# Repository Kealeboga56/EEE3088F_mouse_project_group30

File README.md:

# Micromouse Project: Sensing and Power Subsystems

This repository contains the design files, schematics, and other relevant resources for the sensing and power subsystems of the Micromouse project. The repository is organized into two main folders: `sensing` and `power`.

## Sensing Subsystem

The `sensing` folder contains all the files related to the design and implementation of the sensing subsystem, responsible for obstacle detection and navigation. It includes the following:

- `schematics/`: This directory contains the schematic files for the sensing circuit, including the main schematic and any supplementary schematics.
- `pcb/`: This directory houses the PCB design files, including the board layout, Gerber files, and any other relevant PCB design files.
- `firmware/`: This directory contains the firmware code for the microcontroller used in the sensing subsystem, along with any libraries or dependencies required.
- `simulations/`: This directory includes any simulation files or models used for testing and validating the sensing subsystem's performance.
- `datasheets/`: This directory contains datasheets for the components used in the sensing subsystem, such as sensors, microcontrollers, and other integrated circuits.
- `docs/`: This directory houses any additional documentation or reports related to the sensing subsystem, such as design specifications, test reports, or user manuals.

## Power Subsystem

The `power` folder contains all the files related to the design and implementation of the power subsystem, responsible for power management and distribution. It includes the following:

- `schematics/`: This directory contains the schematic files for the power circuit, including the main schematic and any supplementary schematics.
- `pcb/`: This directory houses the PCB design files for the power subsystem, including the board layout, Gerber files, and any other relevant PCB design files.
- `firmware/`: This directory contains the firmware code for the microcontroller used in the power subsystem (if applicable), along with any libraries or dependencies required.
- `simulations/`: This directory includes any simulation files or models used for testing and validating the power subsystem's performance.
- `datasheets/`: This directory contains datasheets for the components used in the power subsystem, such as regulators, batteries, and other power management components.
- `docs/`: This directory houses any additional documentation or reports related to the power subsystem, such as design specifications, test reports, or user manuals.

## Importing footprints
- For importing footprints in kicad. the easyeda2kicad script was used.
- `Installation/`: run : "pip install easyeda2kicad" on your terminal
- for more on how to get the lcsc_id and how to import visit website [https://pypi.org/project/easyeda2kicad/]

## Contributing

If you would like to contribute to this project, please follow these steps:

1. Fork the repository
2. Create a new branch for your feature or bugfix
3. Commit your changes to the new branch
4. Push the branch to your forked repository
5. Submit a pull request to the main repository

Please ensure that your contributions adhere to the project's coding standards and guidelines.

## License

This project is licensed under the [MIT License](LICENSE).

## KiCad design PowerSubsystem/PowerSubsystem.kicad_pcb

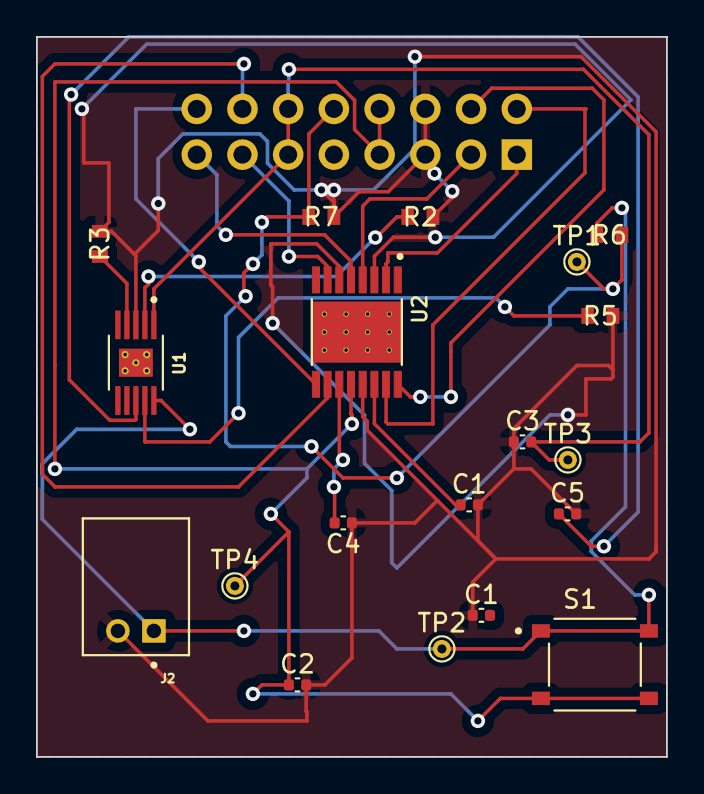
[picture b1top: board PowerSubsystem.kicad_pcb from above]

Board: 2 copper layers, 35.0 x 40.0 mm, 20 parts (1 on the bottom side), 19 nets.

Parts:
C1, C1#2: 2.2uF; C_0402_1005Metric
C2: 10uF; C_0402_1005Metric
C3, C5: 1uF; C_0402_1005Metric
C4: 0.01uF; C_0402_1005Metric
J2: S2B-PH-K-S(LF)(SN); JST_S2B-PH-K-S_LF__SN_
J3: Conn_02x08_Odd_Even; PinHeader_2x08_P2.54mm_Vertical
R2, R5: 1k; BO_CR0603
R3: 2k; BO_CR0603
R6, R7: 100k; BO_CR0603
S1: TS-1187A-B-A-B; SW_TS-1187A-B-A-B
TP1, TP2, TP3, TP4: TestPoint; TestPoint_THTPad_D1.0mm_Drill0.5mm
U1: BQ24092DGQR; IC_XTR111AIDGQR
U2: DRV8833PWPR; IC_DRV8833PWPR

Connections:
5V: C3.2, J3.11, J3.12, TP3.1, U1.1 (IN)
BATT: C2.1, J3.7, J3.8, S1.C, S1.D, TP4.1, U2.12 (VM)
BATT_ADC: J3.10, R6.2, R7.1, TP1.1
BAT_POS: J2.1, R6.1, S1.A, S1.B, TP2.1, U1.10 (OUT)
GND: C1.1, C1#2.2, C2.2, C3.1, C4.1, C5.2, J2.2, J3.5, J3.6, R2.2, R3.2, R5.2, R7.2, U1.3 (VSS), U2.3 (AISEN), U2.6 (BISEN), U2.13 (GND)
Motor1_A: J3.13, U2.7 (BOUT1)
Motor1_B: J3.15, U2.5 (BOUT2)
Motor2_A: J3.1, U2.2 (AOUT1)
Motor2_B: J3.3, U2.4 (AOUT2)
unnamed: R2.1, U1.2 (ISET)
unnamed: R3.1, U1.4 (PRETERM)
unnamed: R5.1, U1.9 (TS)
unnamed: C5.1, U1.8 (~CHG)
unnamed: C4.2, U2.11 (VCP)
unnamed: C1#2.1, U2.14 (VINT)
PWM1: J3.2, U2.15 (AIN2)
PWM2: J3.4, U2.16 (AIN1)
PWM3: J3.14, U2.10 (BIN2)
PWM4: J3.16, U2.9 (BIN1)

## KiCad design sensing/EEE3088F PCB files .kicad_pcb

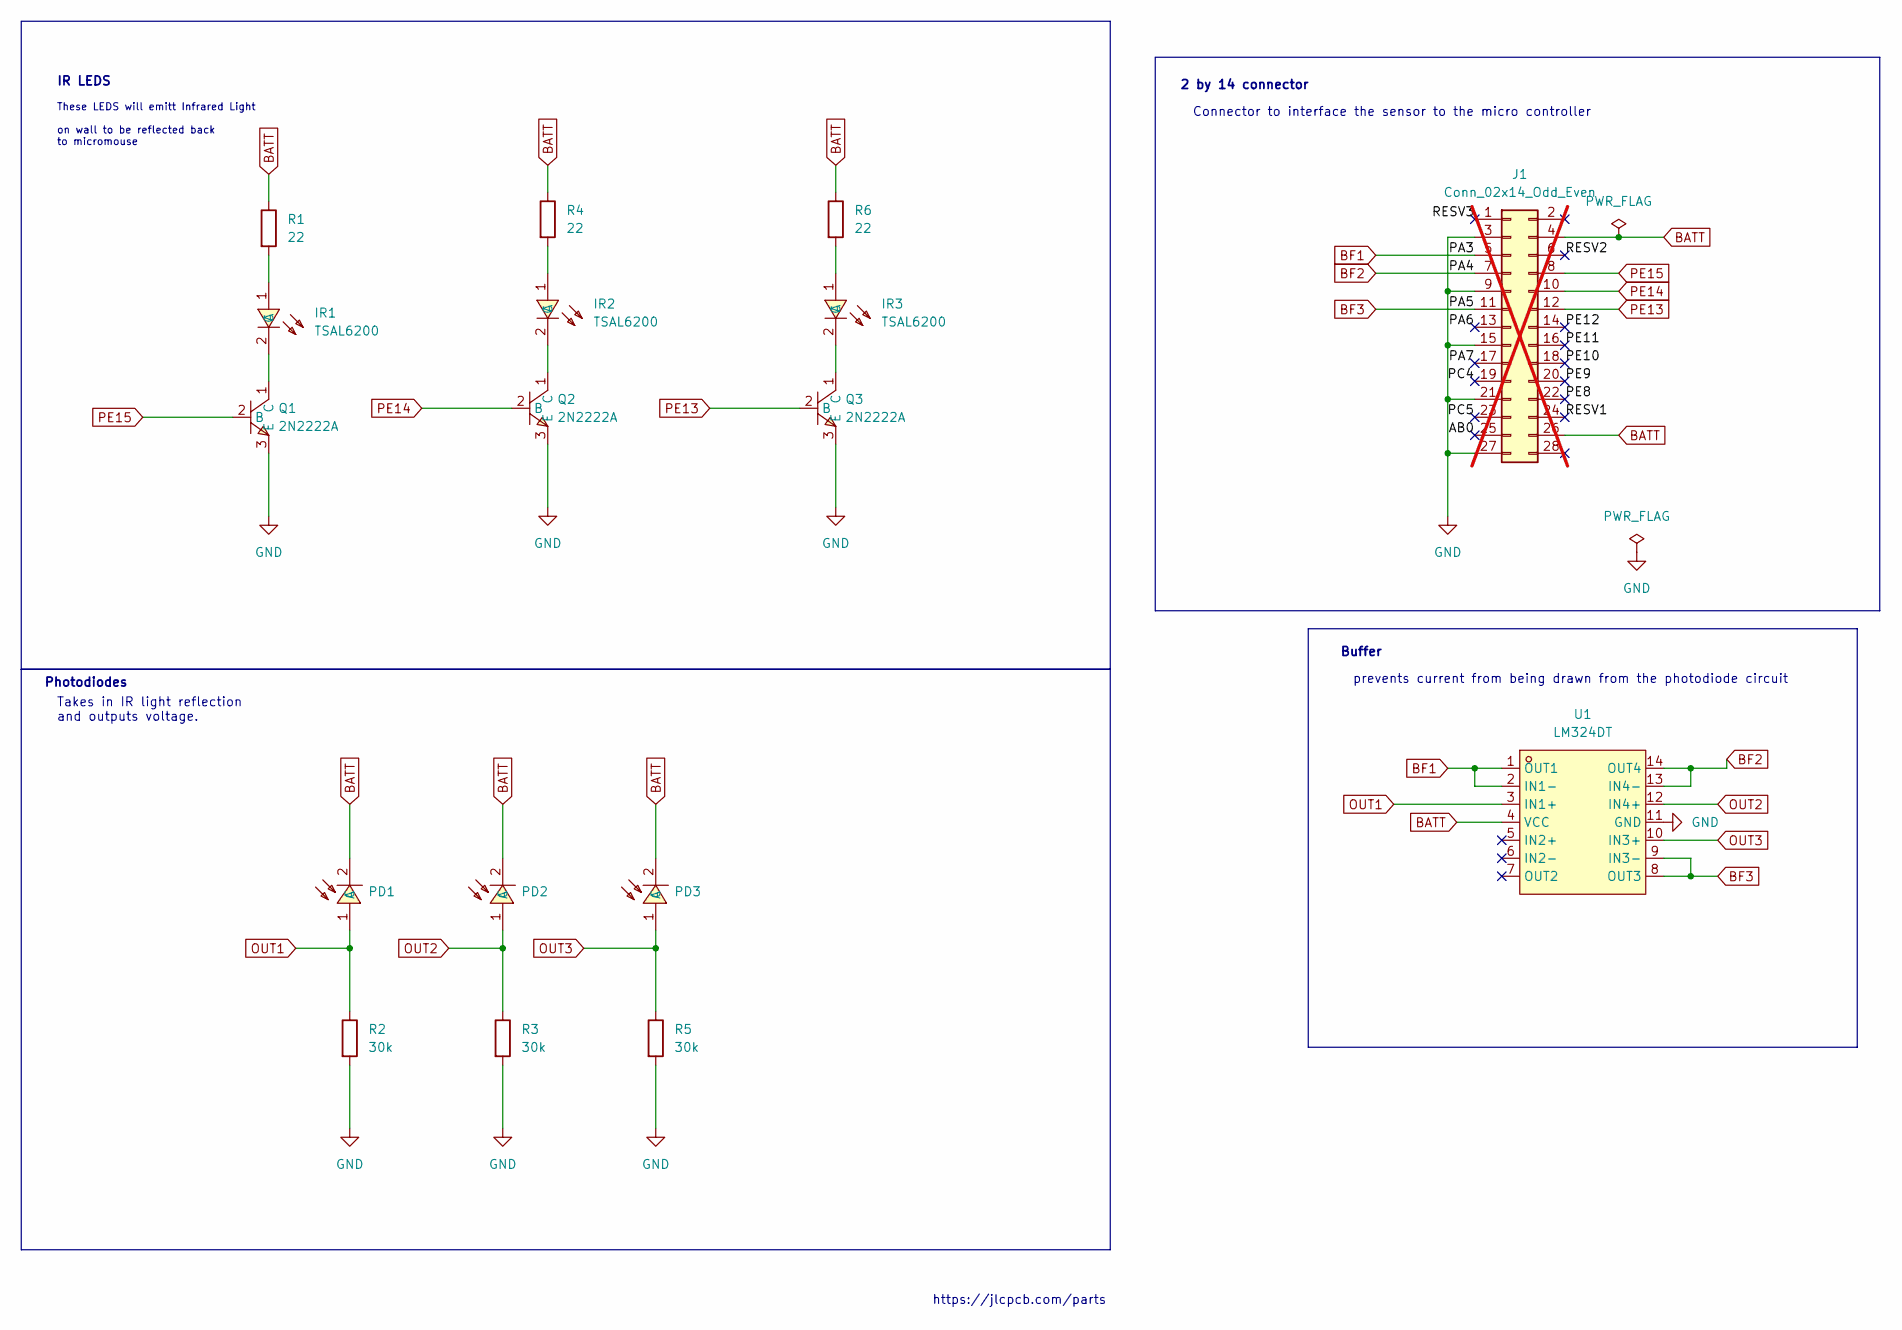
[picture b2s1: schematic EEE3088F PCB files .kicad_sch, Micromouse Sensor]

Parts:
IR1, IR2, IR3: TSAL6200; LED_D5.0mm_Horizontal_O1.27mm_Z3.0mm_IRBlack; LCSC Part C55528
J1: Conn_02x14_Odd_Even; PinHeader_2x14_P2.54mm_Vertical; not fitted
PD1, PD2, PD3: PD333-3B/H0/L2; LED_D5.0mm_Horizontal_O1.27mm_Z3.0mm_IRGrey; LCSC Part C95399
Q1, Q2, Q3: 2N2222A; TO-92-3_L4.8-W3.7-P2.54-R; LCSC Part C358533
R1, R4, R6: 22; R_0805_2012Metric
R2, R3, R5: 30k; R_0805_2012Metric
U1: LM324DT; SOIC-14_L8.7-W3.9-P1.27-LS6.0-BL; LCSC Part C71035

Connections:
/AB0: J1.25
/PA6: J1.13
/PA7: J1.17
/PC4: J1.19
/PC5: J1.23
/PE8: J1.22
/PE9: J1.20
/PE10: J1.18
/PE11: J1.16
/PE12: J1.14
/RESV1: J1.24
/RESV2: J1.6
/RESV3: J1.1
BATT: J1.4, J1.26, PD1.2 (C), PD2.2 (C), PD3.2 (C), R1.1, R4.1, R6.1, U1.4 (VCC)
BF1: J1.5, U1.1 (OUT1), U1.2 (IN1-)
BF2: J1.7, U1.13 (IN4-), U1.14 (OUT4)
BF3: J1.11, U1.8 (OUT3), U1.9 (IN3-)
GND: J1.3, J1.9, J1.15, J1.21, J1.27, Q1.3 (E), Q2.3 (E), Q3.3 (E), R2.2, R3.2, R5.2, U1.11 (GND)
unnamed: IR1.1 (A), R1.2
unnamed: IR1.2 (C), Q1.1 (C)
unnamed: IR2.1 (A), R4.2
unnamed: IR2.2 (C), Q2.1 (C)
unnamed: IR3.1 (A), R6.2
unnamed: IR3.2 (C), Q3.1 (C)
OUT1: PD1.1 (A), R2.1, U1.3 (IN1+)
OUT2: PD2.1 (A), R3.1, U1.12 (IN4+)
OUT3: PD3.1 (A), R5.1, U1.10 (IN3+)
PE13: J1.12, Q3.2 (B)
PE14: J1.10, Q2.2 (B)
PE15: J1.8, Q1.2 (B)

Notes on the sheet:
These LEDS will emitt Infrared Light on wall to be reflected back to micromouse
2 by 14 connector
IR LEDS
Takes in IR light reflection and outputs voltage.
Connector to interface the sensor to the micro controller
prevents current from being drawn from the photodiode circuit
Photodiodes
https://jlcpcb.com/parts
Buffer

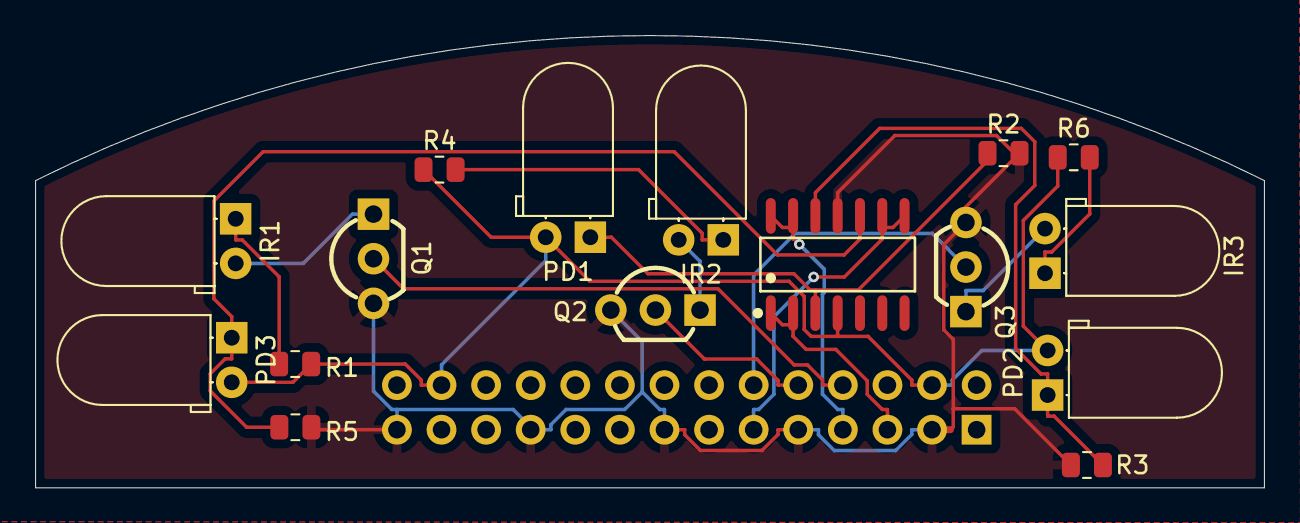
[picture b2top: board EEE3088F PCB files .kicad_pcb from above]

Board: 2 copper layers, 70.0 x 25.8 mm, 17 parts (1 on the bottom side), 17 nets.
